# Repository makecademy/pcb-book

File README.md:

pcb-book
========

Code for the PCB book

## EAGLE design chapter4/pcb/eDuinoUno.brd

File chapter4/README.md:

chapter4
==================

Code for the fourth chapter of the book, which is about designing and building your own Arduino board

- pcb: the PCB of the customized Arduino board for this chapter

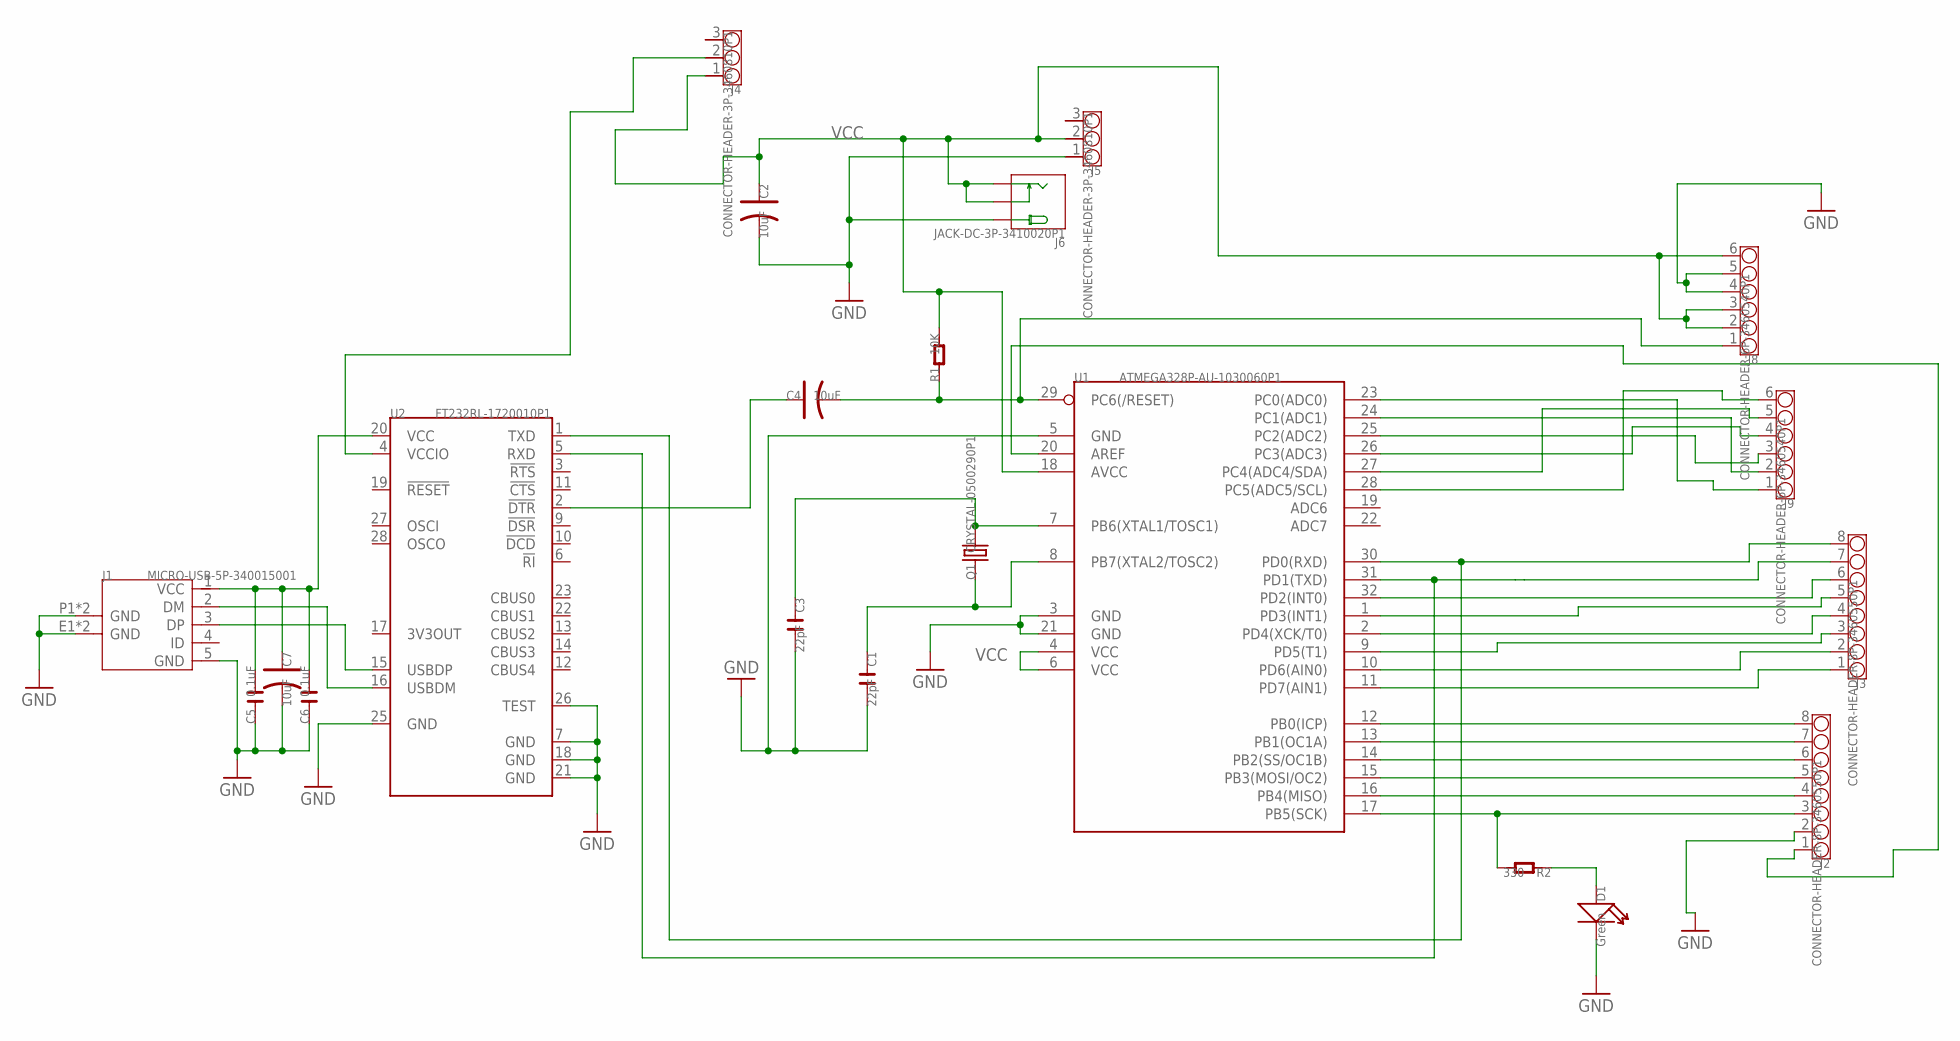
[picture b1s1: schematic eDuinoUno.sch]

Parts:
C1, C3: 22pF; C0603
C2, C4, C7: 10uF; AVX-A
C5, C6: 0.1uF; C0603
D1: Green; LED0603
J1: MICRO-USB-5P-340015001; B-SMD-5P
J2, J3: CONNECTOR-HEADER-8P-3460550P1; 1X8P-2.54-8.5-WHITE-FEMALE
J4, J5: CONNECTOR-HEADER-3P-3460810P1; 1X3P-2.54-2.54-11.6-3.0-BLACK-MALE
J6: JACK-DC-3P-3410020P1; PW-3P-2.1
J8, J9: CONNECTOR-HEADER-6P-3460540P1; 1X6P-2.54-8.5-WHITE-FEMALE
Q1: CRYSTAL-0500290P1; 2P-SMD-5.0X3.2
R1: 10K; R0603
R2: 330; R0603
U1: ATMEGA328P-AU-1030060P1; TQFP32
U2: FT232RL-1720010P1; SSOP28

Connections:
GND: C1.2, C2.- (2), C3.2, C5.1, C6.1, C7.- (2), D1.-, J1.5 (GND), J1.E1 (GND), J1.E2 (GND), J1.P1 (GND), J1.P2 (GND), J2.2, J5.1, J6.+, J8.4, J8.5, U1.3 (GND), U1.5 (GND), U1.21 (GND), U2.7 (GND), U2.18 (GND), U2.21 (GND), U2.25 (GND), U2.26 (TEST)
unnamed: J9.1, U1.23 (PC0(ADC0))
unnamed: J9.2, U1.24 (PC1(ADC1))
unnamed: J9.3, U1.25 (PC2(ADC2))
unnamed: C1.1, Q1.1, U1.8 (PB7(XTAL2/TOSC2))
unnamed: J9.5, U1.27 (PC4(ADC4/SDA))
unnamed: J9.6, U1.28 (PC5(ADC5/SCL))
unnamed: J3.8, U1.30 (PD0(RXD)), U2.1 (TXD)
unnamed: J3.7, U1.31 (PD1(TXD)), U2.5 (RXD)
unnamed: C5.2, C6.2, C7.+ (1), J1.1 (VCC), U2.20 (VCC)
unnamed: J1.2 (DM), U2.16 (USBDM)
unnamed: J3.6, U1.32 (PD2(INT0))
unnamed: J2.3, R2.2, U1.17 (PB5(SCK))
unnamed: J2.4, U1.16 (PB4(MISO))
unnamed: J2.5, U1.15 (PB3(MOSI/OC2))
unnamed: J3.5, U1.1 (PD3(INT1))
unnamed: J9.4, U1.26 (PC3(ADC3))
unnamed: J3.3, U1.9 (PD5(T1))
unnamed: J3.2, U1.10 (PD6(AIN0))
unnamed: J1.3 (DP), U2.15 (USBDP)
unnamed: C4.+ (1), U2.2 (!DTR)
unnamed: J4.2, U2.4 (VCCIO)
unnamed: C4.- (2), J8.1, R1.1, U1.29 (PC6(/RESET))
unnamed: J2.8, U1.12 (PB0(ICP))
unnamed: J2.7, U1.13 (PB1(OC1A))
unnamed: J2.6, U1.14 (PB2(SS/OC1B))
unnamed: J3.4, U1.2 (PD4(XCK/T0))
unnamed: J2.1, U1.20 (AREF)
unnamed: J3.1, U1.11 (PD7(AIN1))
unnamed: D1.+, R2.1
VCC: C2.+ (1), J4.1, J5.2, J6.-1 (-), J6.-2 (CDN), J8.2, J8.3, J8.6, R1.2, U1.4 (VCC), U1.6 (VCC), U1.18 (AVCC)
XTAL2: C3.1, Q1.2, U1.7 (PB6(XTAL1/TOSC1))

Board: 2 copper layers, 21 parts (0 on the bottom side), 32 nets, no tracks yet.

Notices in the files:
parts and their libraries:
SparkFun-Aesthetics: Licensing: Creative Commons ShareAlike 4.0 International - https://creativecommons.org/licenses/by-sa/4.0
